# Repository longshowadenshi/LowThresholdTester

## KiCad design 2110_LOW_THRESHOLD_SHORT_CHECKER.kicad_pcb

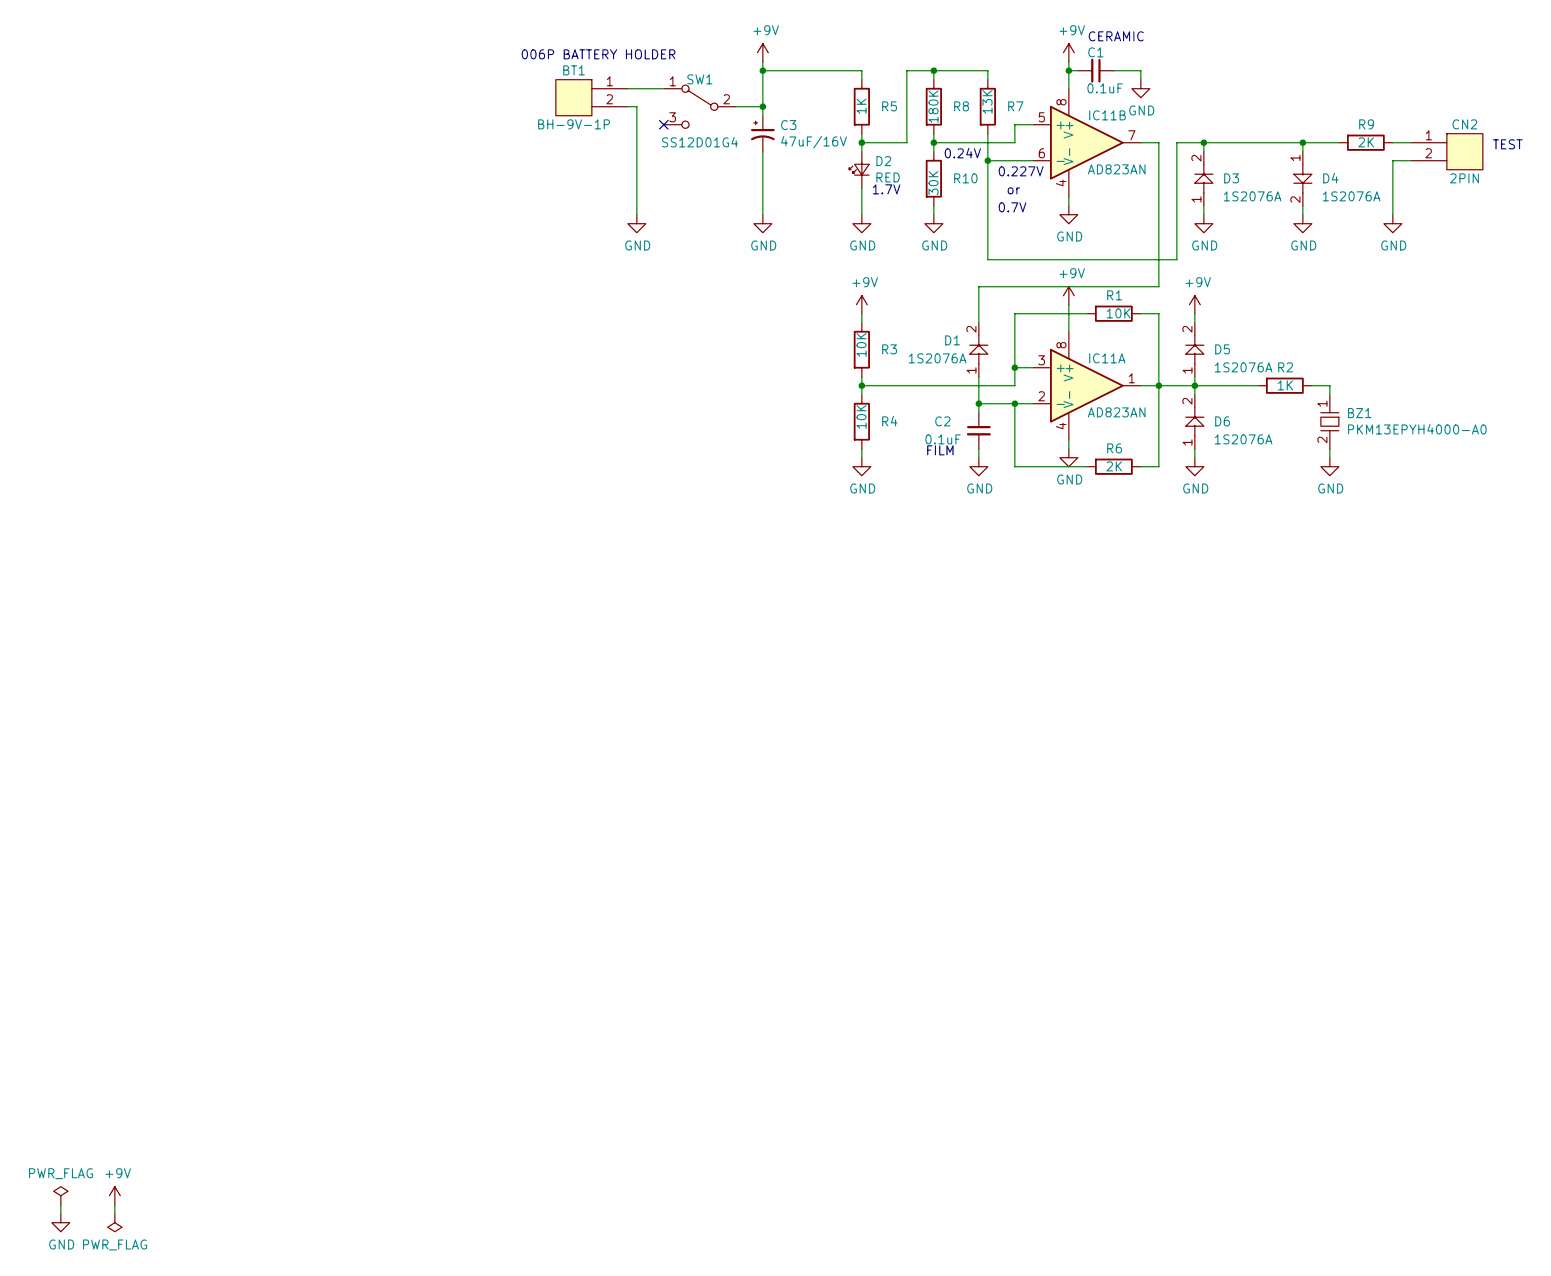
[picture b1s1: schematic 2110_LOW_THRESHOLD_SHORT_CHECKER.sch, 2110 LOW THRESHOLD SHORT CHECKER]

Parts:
BT1: BH-9V-1P; XH-2pins
BZ1: PKM13EPYH4000-A0
C1: 0.1uF; ceramic
C2: 0.1uF; film
C3: 47uF/16V; C_47uf-16v
CN2: 2PIN; S2B-XH-A
D1, D3, D4, D5, D6: 1S2076A
D2: RED; LED_HLMP4700
IC11: AD823AN; ic_DIP-8_W7.62mm
R1, R3, R4: 10K; R
R2, R5: 1K; R
R6, R9: 2K; R
R7: 13K; R
R8: 180K; R
R10: 30K; R
SW1: SS12D01G4; AS1D 47

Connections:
+9V: C1.2, C3.1, D5.2, IC11.8 (V+), R3.1, R5.1, SW1.2 (B)
GND: BT1.2, BZ1.2, C1.1, C2.2, C3.2, CN2.2, D2.2 (K), D3.1, D4.2, D6.1, IC11.4 (V-), R4.2, R10.2
unnamed: BT1.1, SW1.1 (A)
unnamed: BZ1.1, R2.1
unnamed: C2.1, D1.1, IC11.2 (-), R6.2
unnamed: CN2.1, R9.1
unnamed: D1.2, IC11.7
unnamed: D2.1 (A), R5.2, R7.1, R8.1
unnamed: D3.2, D4.1, IC11.6 (-), R7.2, R9.2
unnamed: D5.1, D6.2, IC11.1, R1.1, R2.2, R6.1
unnamed: IC11.3 (+), R1.2, R3.2, R4.1
unnamed: IC11.5 (+), R8.2, R10.1

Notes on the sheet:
FILM
CERAMIC
006P BATTERY HOLDER
TEST
1.7V
0.24V
0.227V
0.7V

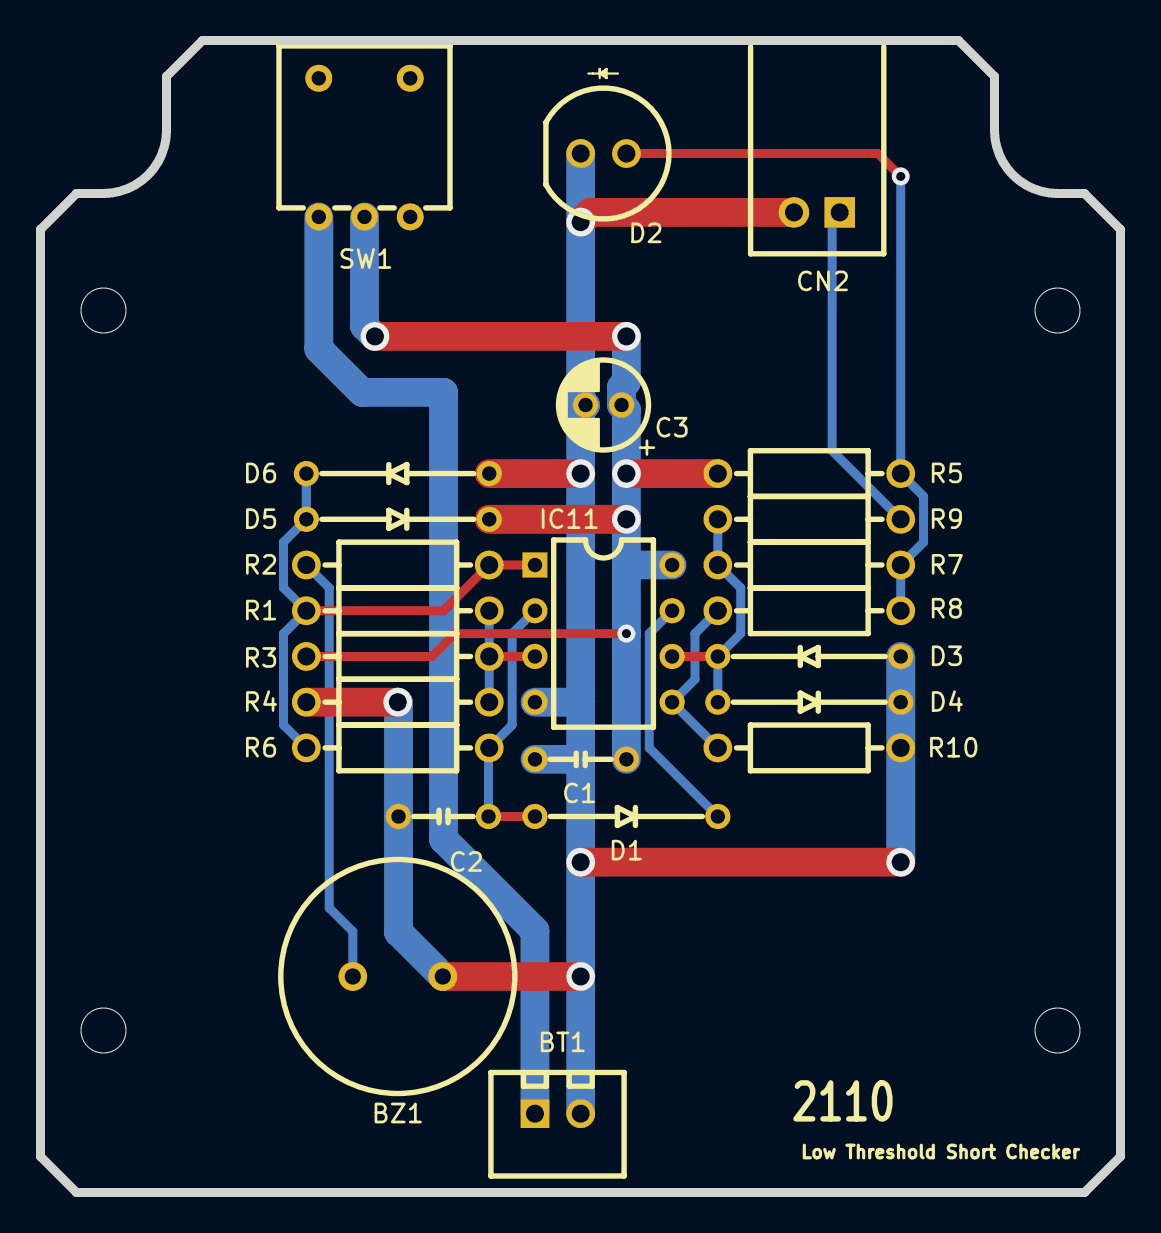
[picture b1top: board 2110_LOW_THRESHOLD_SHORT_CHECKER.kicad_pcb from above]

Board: 2 copper layers, 60.0 x 64.0 mm, 24 parts (0 on the bottom side), 12 nets.

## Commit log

2021-08-26 一部回路と、パターンの修正。
